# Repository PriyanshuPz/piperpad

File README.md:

# PiperPad

a tiny 3×3 hackpad with per-key RGB light. 
Each of the 9 keys has its own RGB LED. Instead of just pressing buttons, you can enter **sequences** and **patterns** that unlock behaviors, layers, or macros.
It is built to make secure passcode patterns with different Led lights.

---

## Hackpad Overview

---

## Schematic

---

## PCB

---

## Case Design

---

## Firmware

> Firmware is almost done

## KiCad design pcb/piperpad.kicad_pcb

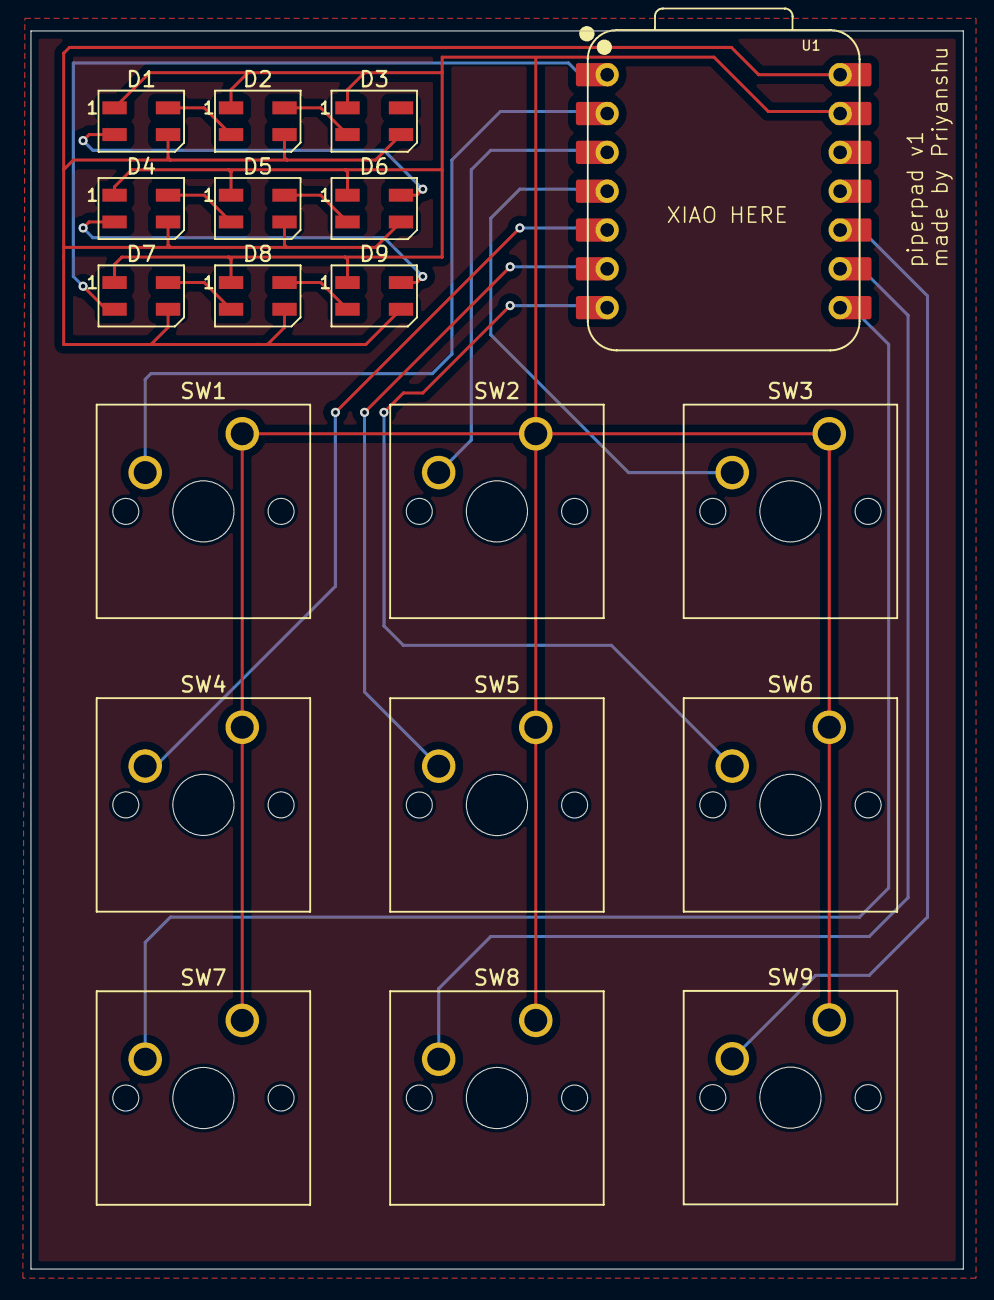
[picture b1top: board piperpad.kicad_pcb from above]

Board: 2 copper layers, 61.0 x 81.0 mm, 19 parts (0 on the bottom side), 20 nets.

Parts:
D1, D2, D3, D4, D5, D6, D7, D8, D9: SK6812; LED_SK6812MINI_PLCC4_3.5x3.5mm_P1.75mm
SW1, SW2, SW3, SW4, SW5, SW6, SW7, SW8, SW9: SW_Push; SW_Cherry_MX_1.00u_PCB
U1: XIAO-RP2040-DIP

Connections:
+5V: D1.3 (VDD), D2.3 (VDD), D3.3 (VDD), D4.3 (VDD), D5.3 (VDD), D6.3 (VDD), D7.3 (VDD), D8.3 (VDD), D9.3 (VDD), U1.14 (VBUS)
GND: D1.1 (VSS), D2.1 (VSS), D3.1 (VSS), D4.1 (VSS), D5.1 (VSS), D6.1 (VSS), D7.1 (VSS), D8.1 (VSS), D9.1 (VSS), SW1.1, SW2.1, SW3.1, SW4.1, SW5.1, SW6.1, SW7.1, SW8.1, SW9.1, U1.13 (GND)
unnamed: D1.2 (DIN), D6.4 (DOUT)
unnamed: D1.4 (DOUT), D2.2 (DIN)
unnamed: D2.4 (DOUT), D3.2 (DIN)
unnamed: D4.2 (DIN), D9.4 (DOUT)
unnamed: D4.4 (DOUT), D5.2 (DIN)
unnamed: D5.4 (DOUT), D6.2 (DIN)
unnamed: D7.2 (DIN), U1.1 (GPIO26/ADC0/A0)
unnamed: D7.4 (DOUT), D8.2 (DIN)
unnamed: D8.4 (DOUT), D9.2 (DIN)
unnamed: SW6.2, U1.7 (GPIO0/TX)
unnamed: SW7.2, U1.8 (GPIO1/RX)
unnamed: SW8.2, U1.9 (GPIO2/SCK)
unnamed: SW9.2, U1.10 (GPIO4/MISO)
unnamed: SW4.2, U1.5 (GPIO6/SDA)
unnamed: SW5.2, U1.6 (GPIO7/SCL)
unnamed: SW1.2, U1.2 (GPIO27/ADC1/A1)
unnamed: SW2.2, U1.3 (GPIO28/ADC2/A2)
unnamed: SW3.2, U1.4 (GPIO29/ADC3/A3)

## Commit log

2026-01-12 initial PoC files for piperpad
2026-01-13 Added 3d models and exported pcb
2026-01-13 updated readme file with information
2026-01-13 Updated latest fixed cad models and final after assembly check
2026-03-02 chore: updated ths status of the project
2026-03-04 project status
2026-03-11 readme update please
2026-05-05 readme chore
2026-05-06 readme firmware update
